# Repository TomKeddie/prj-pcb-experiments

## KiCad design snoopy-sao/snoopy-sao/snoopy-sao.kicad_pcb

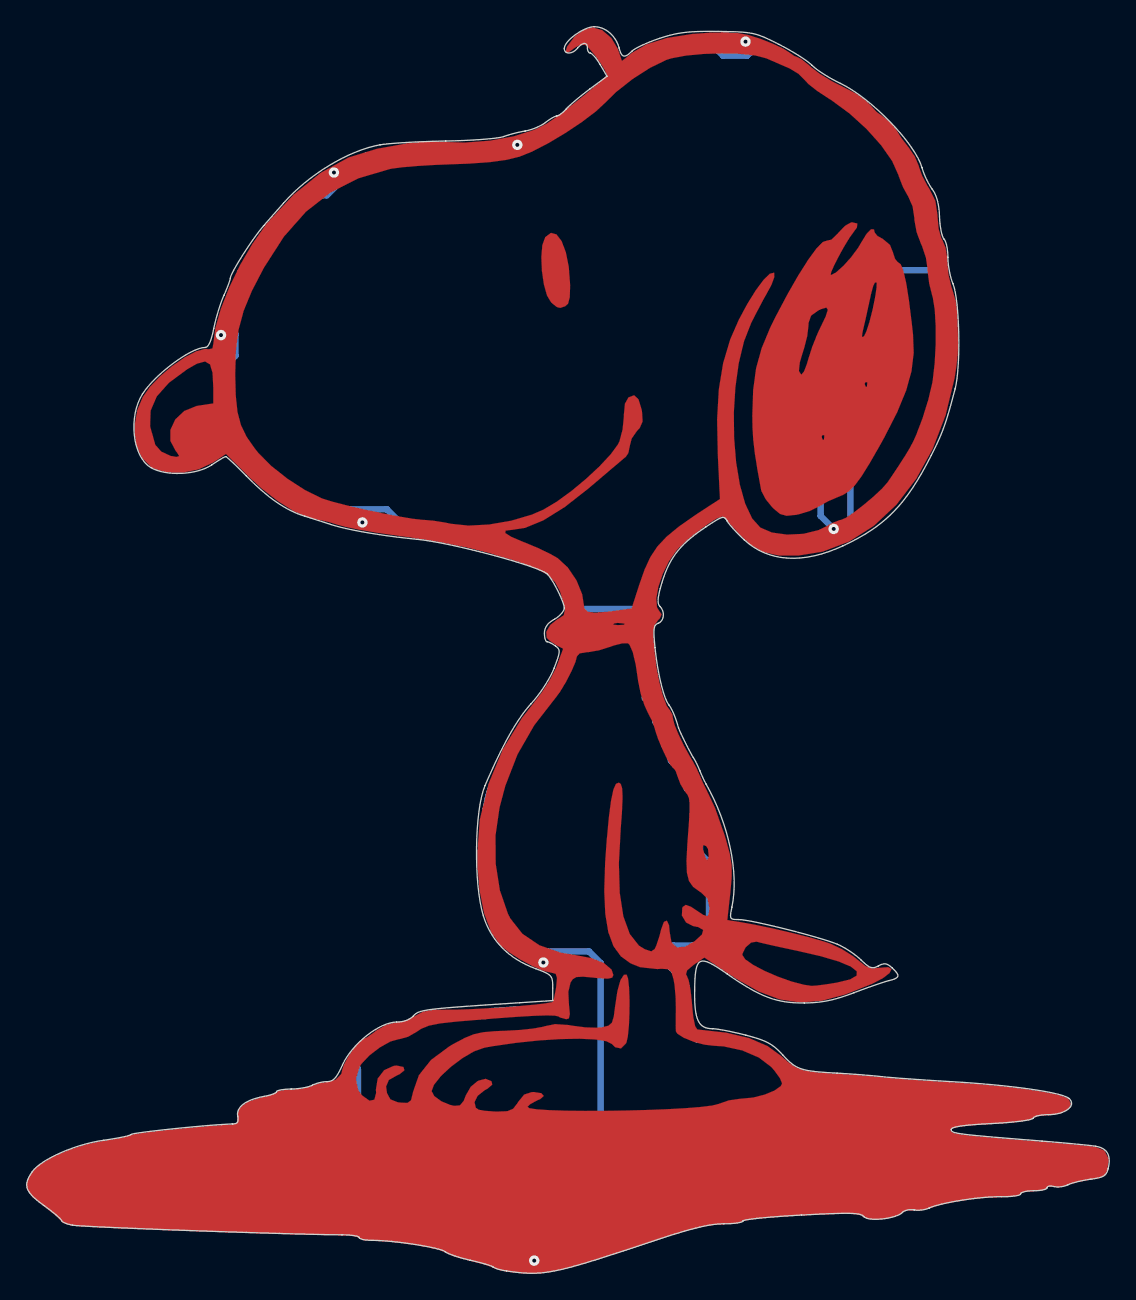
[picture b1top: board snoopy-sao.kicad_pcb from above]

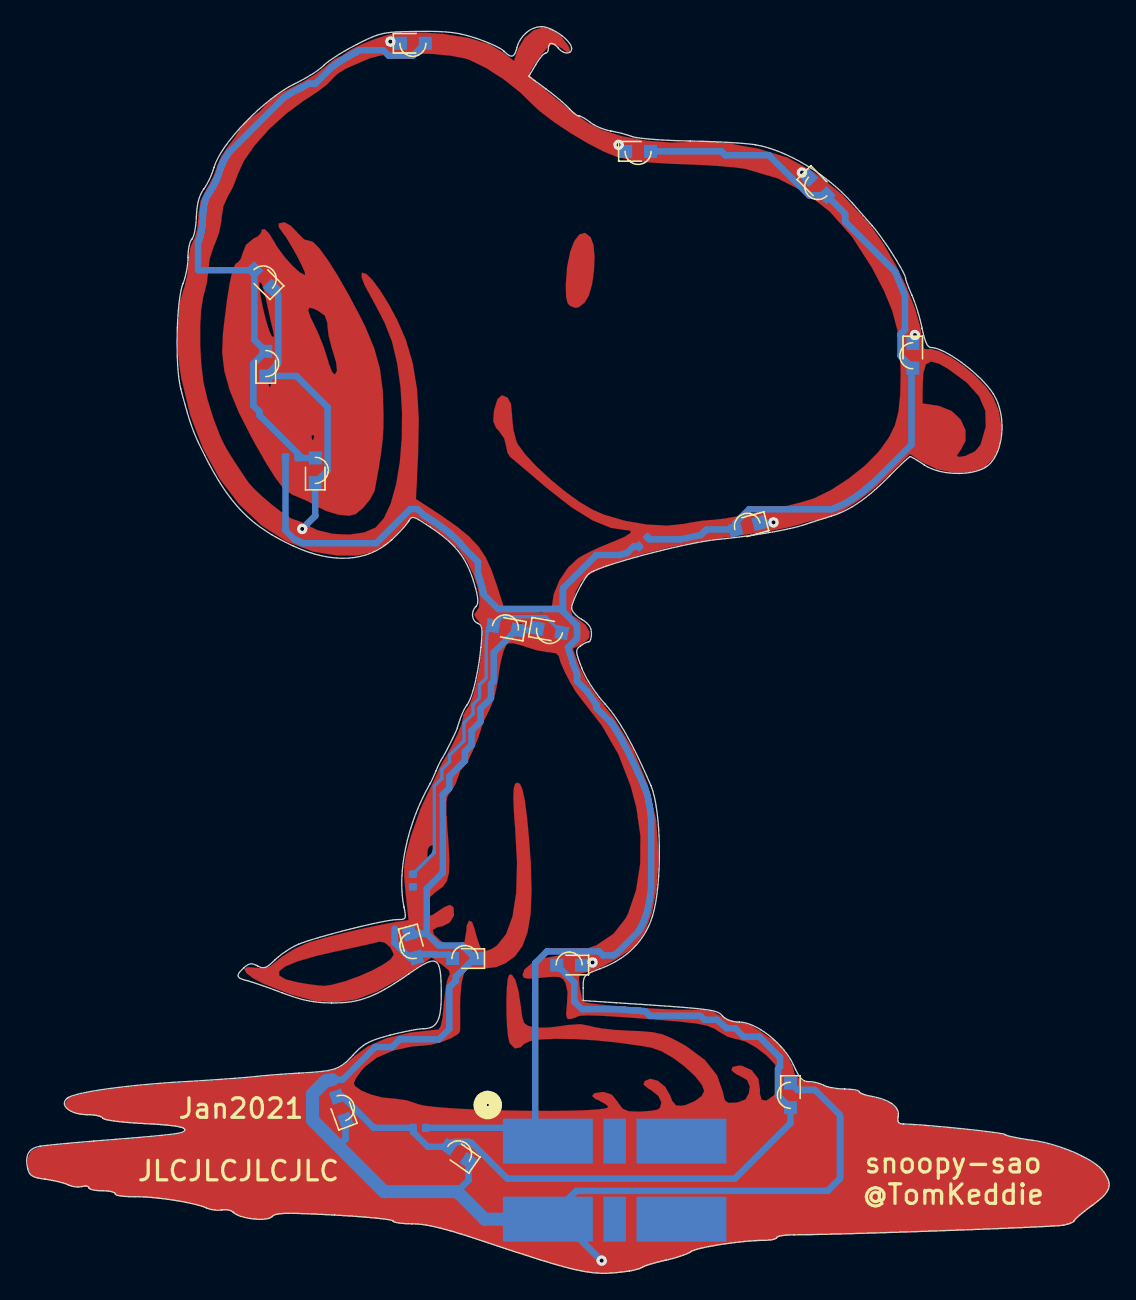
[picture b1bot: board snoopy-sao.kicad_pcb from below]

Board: 2 copper layers, 83.1 x 95.8 mm, 24 parts (21 on the bottom side), 6 nets.

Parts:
D1, D2, D3, D4, D5, D6, D7, D8, D9, D10, D11, D12, D13, D14, D15, D16: LED; ALIEXPRESS_LED_SIDE_0602
H1: front-mask; snoopy-sao-front-mask-invert
H2: front-copper; snoopy-sao-front-copper
H3: back-mask; snoopy-sao-back-mask-invert
R1, R2, R3, R4: 100R; R_0402_1005Metric
X1: Badgelife_sao_connector_v169bis; Badgelife-SAOv169-SAO-2x3-SMD-BIGPADS

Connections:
+3V3: R1.1, R2.1, R3.1, R4.1, X1.1
/A_1: D1.2, D2.2, D3.2, D4.2, R1.2
/A_2: D5.2, D6.2, D7.2, D8.2, R2.2
/A_3: D9.2, D10.2, D11.2, D12.2, R3.2
/A_4: D13.2, D14.2, D15.2, D16.2, R4.2
GND: D1.1, D2.1, D3.1, D4.1, D5.1, D6.1, D7.1, D8.1, D9.1, D10.1, D11.1, D12.1, D13.1, D14.1, D15.1, D16.1, H2.1, X1.2

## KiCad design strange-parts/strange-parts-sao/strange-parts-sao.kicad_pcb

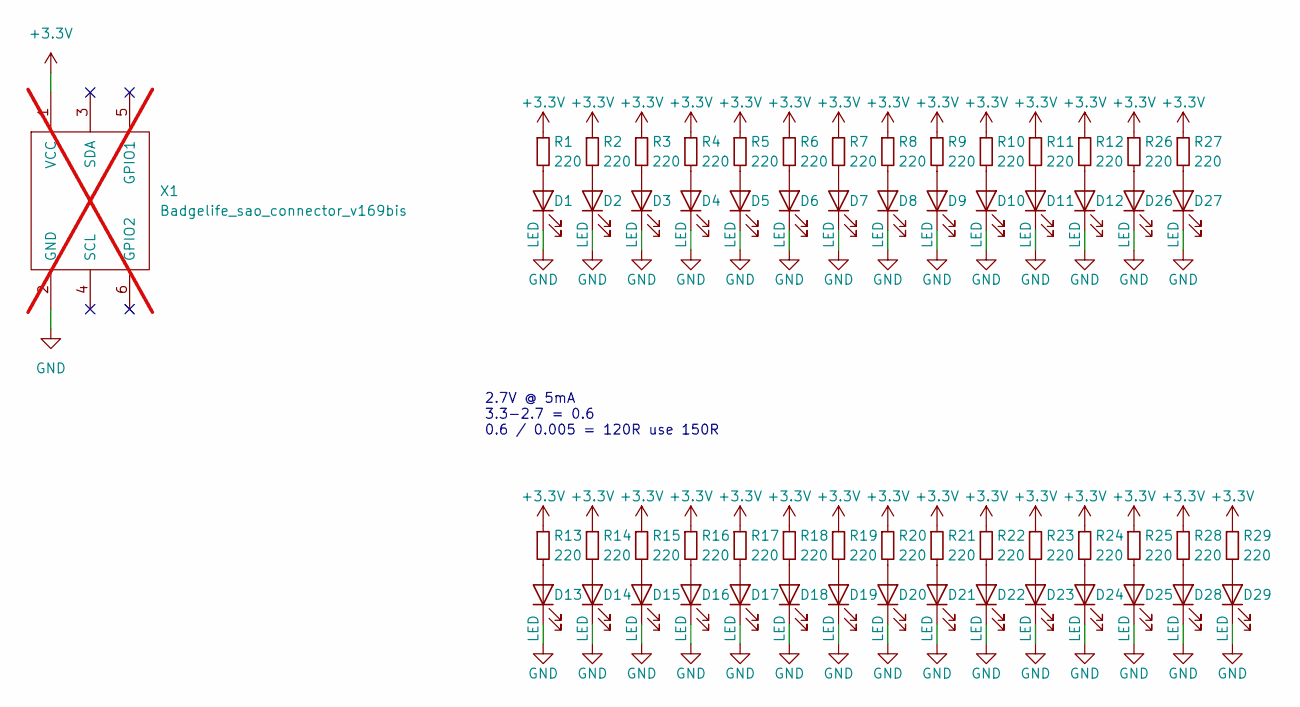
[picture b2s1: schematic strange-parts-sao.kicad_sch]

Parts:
D1, D2, D3, D4, D5, D6, D7, D8, D9, D10, D11, D12, D13, D14, D15, D16, D17, D18, D19, D20, D21, D22, D23, D24, D25, D26, D27, D28, D29: LED; JLCPCB_SIDE_C409529; LCSC C409529
R1, R2, R3, R4, R5, R6, R7, R8, R9, R10, R11, R12, R13, R14, R15, R16, R17, R18, R19, R20, R21, R22, R23, R24, R25, R26, R27, R28, R29: 220; R_0402_1005Metric; MFGPN 0402WGF2200TCE; LCSC C25091
X1: Badgelife_sao_connector_v169bis; Badgelife-SAOv169-SAO-2x3-SMD-BIGPADS; not fitted

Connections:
+3.3V: R1.1, R2.1, R3.1, R4.1, R5.1, R6.1, R7.1, R8.1, R9.1, R10.1, R11.1, R12.1, R13.1, R14.1, R15.1, R16.1, R17.1, R18.1, R19.1, R20.1, R21.1, R22.1, R23.1, R24.1, R25.1, R26.1, R27.1, R28.1, R29.1, X1.1 (VCC)
GND: D1.1 (K), D2.1 (K), D3.1 (K), D4.1 (K), D5.1 (K), D6.1 (K), D7.1 (K), D8.1 (K), D9.1 (K), D10.1 (K), D11.1 (K), D12.1 (K), D13.1 (K), D14.1 (K), D15.1 (K), D16.1 (K), D17.1 (K), D18.1 (K), D19.1 (K), D20.1 (K), D21.1 (K), D22.1 (K), D23.1 (K), D24.1 (K), D25.1 (K), D26.1 (K), D27.1 (K), D28.1 (K), D29.1 (K), X1.2 (GND)
unnamed: D1.2 (A), R1.2
unnamed: D2.2 (A), R2.2
unnamed: D3.2 (A), R3.2
unnamed: D4.2 (A), R4.2
unnamed: D5.2 (A), R5.2
unnamed: D6.2 (A), R6.2
unnamed: D7.2 (A), R7.2
unnamed: D8.2 (A), R8.2
unnamed: D9.2 (A), R9.2
unnamed: D10.2 (A), R10.2
unnamed: D11.2 (A), R11.2
unnamed: D12.2 (A), R12.2
unnamed: D13.2 (A), R13.2
unnamed: D14.2 (A), R14.2
unnamed: D15.2 (A), R15.2
unnamed: D16.2 (A), R16.2
unnamed: D17.2 (A), R17.2
unnamed: D18.2 (A), R18.2
unnamed: D19.2 (A), R19.2
unnamed: D20.2 (A), R20.2
unnamed: D21.2 (A), R21.2
unnamed: D22.2 (A), R22.2
unnamed: D23.2 (A), R23.2
unnamed: D24.2 (A), R24.2
unnamed: D25.2 (A), R25.2
unnamed: D26.2 (A), R26.2
unnamed: D27.2 (A), R27.2
unnamed: D28.2 (A), R28.2
unnamed: D29.2 (A), R29.2

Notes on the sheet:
2.7V @ 5mA 3.3-2.7 = 0.6 0.6 / 0.005 = 120R use 150R

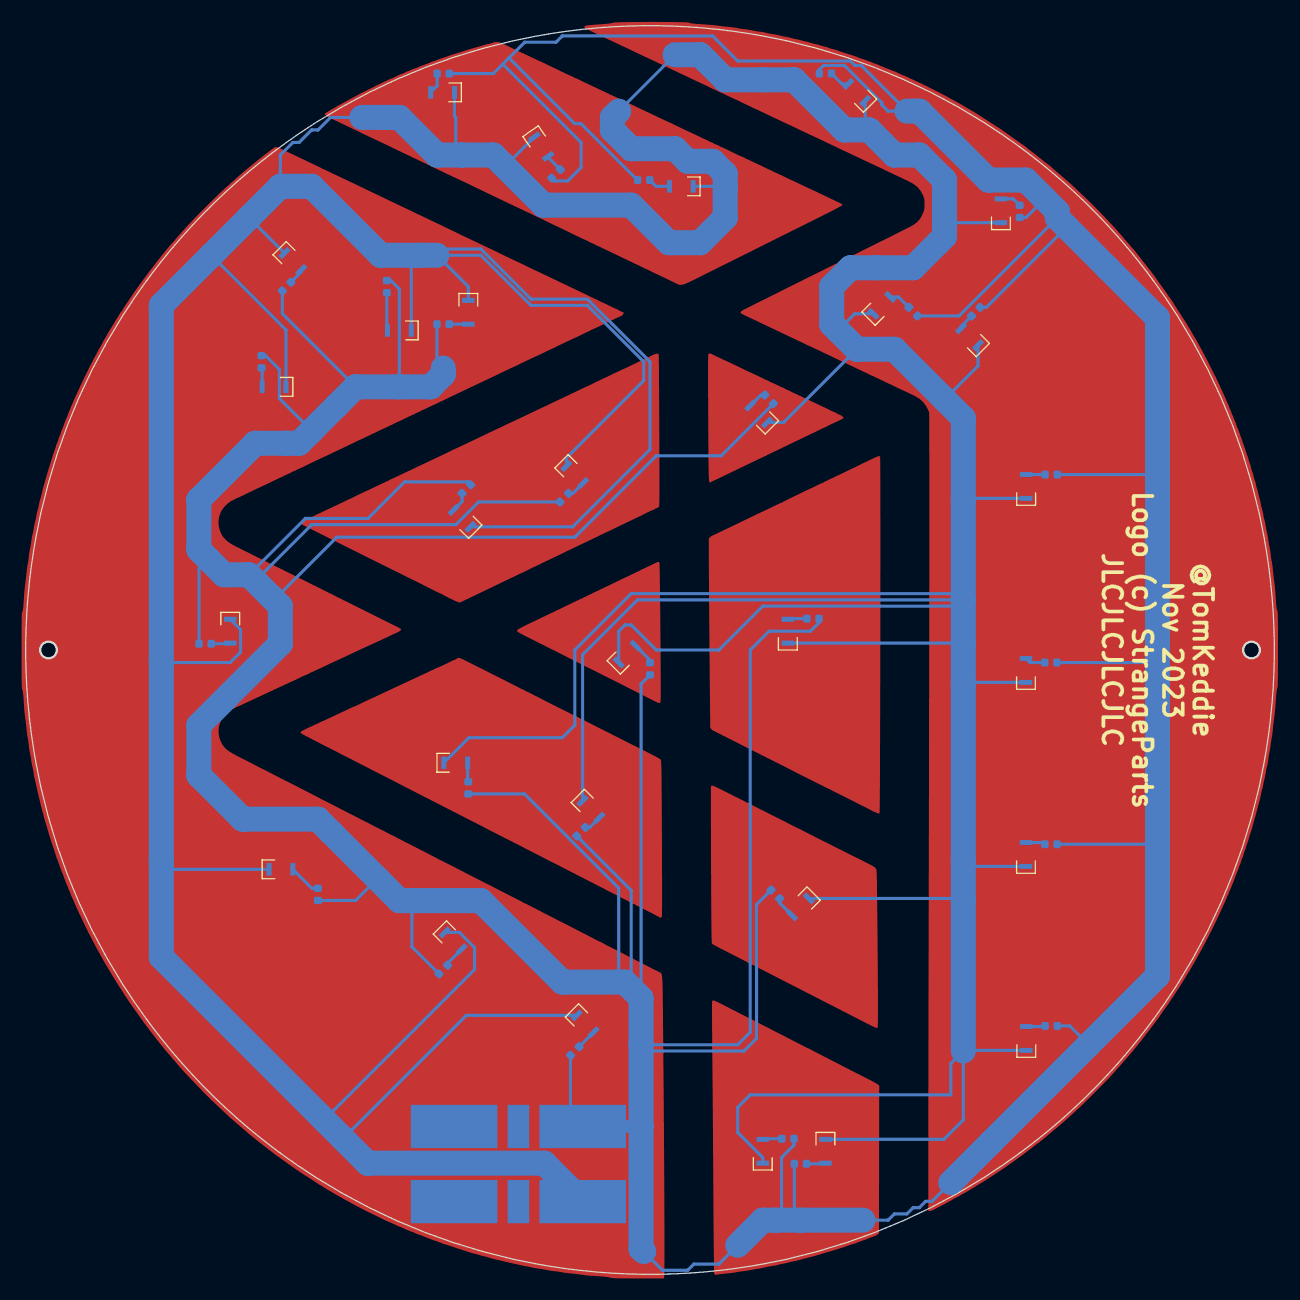
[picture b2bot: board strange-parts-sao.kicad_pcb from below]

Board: 2 copper layers, 99.6 x 99.6 mm, 59 parts (59 on the bottom side), 31 nets.

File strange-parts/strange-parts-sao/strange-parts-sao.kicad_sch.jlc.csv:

"Comment","Designator","Footprint","LCSC"
"LED","D1","tom-opto:JLCPCB_SIDE_C409529","C409529","",""
"LED","D2","tom-opto:JLCPCB_SIDE_C409529","C409529","",""
"LED","D3","tom-opto:JLCPCB_SIDE_C409529","C409529","",""
"LED","D4","tom-opto:JLCPCB_SIDE_C409529","C409529","",""
"LED","D5","tom-opto:JLCPCB_SIDE_C409529","C409529","",""
"LED","D6","tom-opto:JLCPCB_SIDE_C409529","C409529","",""
"LED","D7","tom-opto:JLCPCB_SIDE_C409529","C409529","",""
"LED","D8","tom-opto:JLCPCB_SIDE_C409529","C409529","",""
"LED","D9","tom-opto:JLCPCB_SIDE_C409529","C409529","",""
"LED","D10","tom-opto:JLCPCB_SIDE_C409529","C409529","",""
"LED","D11","tom-opto:JLCPCB_SIDE_C409529","C409529","",""
"LED","D12","tom-opto:JLCPCB_SIDE_C409529","C409529","",""
"LED","D13","tom-opto:JLCPCB_SIDE_C409529","C409529","",""
"LED","D14","tom-opto:JLCPCB_SIDE_C409529","C409529","",""
"LED","D15","tom-opto:JLCPCB_SIDE_C409529","C409529","",""
"LED","D16","tom-opto:JLCPCB_SIDE_C409529","C409529","",""
"LED","D17","tom-opto:JLCPCB_SIDE_C409529","C409529","",""
"LED","D18","tom-opto:JLCPCB_SIDE_C409529","C409529","",""
"LED","D19","tom-opto:JLCPCB_SIDE_C409529","C409529","",""
"LED","D20","tom-opto:JLCPCB_SIDE_C409529","C409529","",""
"LED","D21","tom-opto:JLCPCB_SIDE_C409529","C409529","",""
"LED","D22","tom-opto:JLCPCB_SIDE_C409529","C409529","",""
"LED","D23","tom-opto:JLCPCB_SIDE_C409529","C409529","",""
"LED","D24","tom-opto:JLCPCB_SIDE_C409529","C409529","",""
"LED","D25","tom-opto:JLCPCB_SIDE_C409529","C409529","",""
"LED","D26","tom-opto:JLCPCB_SIDE_C409529","C409529","",""
"LED","D27","tom-opto:JLCPCB_SIDE_C409529","C409529","",""
"LED","D28","tom-opto:JLCPCB_SIDE_C409529","C409529","",""
"LED","D29","tom-opto:JLCPCB_SIDE_C409529","C409529","",""
"220","R1","R_0402_1005Metric","C25091","UNI-ROYAL(Uniroyal Elec)","0402WGF2200TCE"
"220","R2","R_0402_1005Metric","C25091","UNI-ROYAL(Uniroyal Elec)","0402WGF2200TCE"
"220","R3","R_0402_1005Metric","C25091","UNI-ROYAL(Uniroyal Elec)","0402WGF2200TCE"
"220","R4","R_0402_1005Metric","C25091","UNI-ROYAL(Uniroyal Elec)","0402WGF2200TCE"
"220","R5","R_0402_1005Metric","C25091","UNI-ROYAL(Uniroyal Elec)","0402WGF2200TCE"
"220","R6","R_0402_1005Metric","C25091","UNI-ROYAL(Uniroyal Elec)","0402WGF2200TCE"
"220","R7","R_0402_1005Metric","C25091","UNI-ROYAL(Uniroyal Elec)","0402WGF2200TCE"
"220","R8","R_0402_1005Metric","C25091","UNI-ROYAL(Uniroyal Elec)","0402WGF2200TCE"
"220","R9","R_0402_1005Metric","C25091","UNI-ROYAL(Uniroyal Elec)","0402WGF2200TCE"
"220","R10","R_0402_1005Metric","C25091","UNI-ROYAL(Uniroyal Elec)","0402WGF2200TCE"
"220","R11","R_0402_1005Metric","C25091","UNI-ROYAL(Uniroyal Elec)","0402WGF2200TCE"
"220","R12","R_0402_1005Metric","C25091","UNI-ROYAL(Uniroyal Elec)","0402WGF2200TCE"
"220","R13","R_0402_1005Metric","C25091","UNI-ROYAL(Uniroyal Elec)","0402WGF2200TCE"
"220","R14","R_0402_1005Metric","C25091","UNI-ROYAL(Uniroyal Elec)","0402WGF2200TCE"
"220","R15","R_0402_1005Metric","C25091","UNI-ROYAL(Uniroyal Elec)","0402WGF2200TCE"
"220","R16","R_0402_1005Metric","C25091","UNI-ROYAL(Uniroyal Elec)","0402WGF2200TCE"
"220","R17","R_0402_1005Metric","C25091","UNI-ROYAL(Uniroyal Elec)","0402WGF2200TCE"
"220","R18","R_0402_1005Metric","C25091","UNI-ROYAL(Uniroyal Elec)","0402WGF2200TCE"
"220","R19","R_0402_1005Metric","C25091","UNI-ROYAL(Uniroyal Elec)","0402WGF2200TCE"
"220","R20","R_0402_1005Metric","C25091","UNI-ROYAL(Uniroyal Elec)","0402WGF2200TCE"
"220","R21","R_0402_1005Metric","C25091","UNI-ROYAL(Uniroyal Elec)","0402WGF2200TCE"
"220","R22","R_0402_1005Metric","C25091","UNI-ROYAL(Uniroyal Elec)","0402WGF2200TCE"
"220","R23","R_0402_1005Metric","C25091","UNI-ROYAL(Uniroyal Elec)","0402WGF2200TCE"
"220","R24","R_0402_1005Metric","C25091","UNI-ROYAL(Uniroyal Elec)","0402WGF2200TCE"
"220","R25","R_0402_1005Metric","C25091","UNI-ROYAL(Uniroyal Elec)","0402WGF2200TCE"
"220","R26","R_0402_1005Metric","C25091","UNI-ROYAL(Uniroyal Elec)","0402WGF2200TCE"
"220","R27","R_0402_1005Metric","C25091","UNI-ROYAL(Uniroyal Elec)","0402WGF2200TCE"
"220","R28","R_0402_1005Metric","C25091","UNI-ROYAL(Uniroyal Elec)","0402WGF2200TCE"
"220","R29","R_0402_1005Metric","C25091","UNI-ROYAL(Uniroyal Elec)","0402WGF2200TCE"

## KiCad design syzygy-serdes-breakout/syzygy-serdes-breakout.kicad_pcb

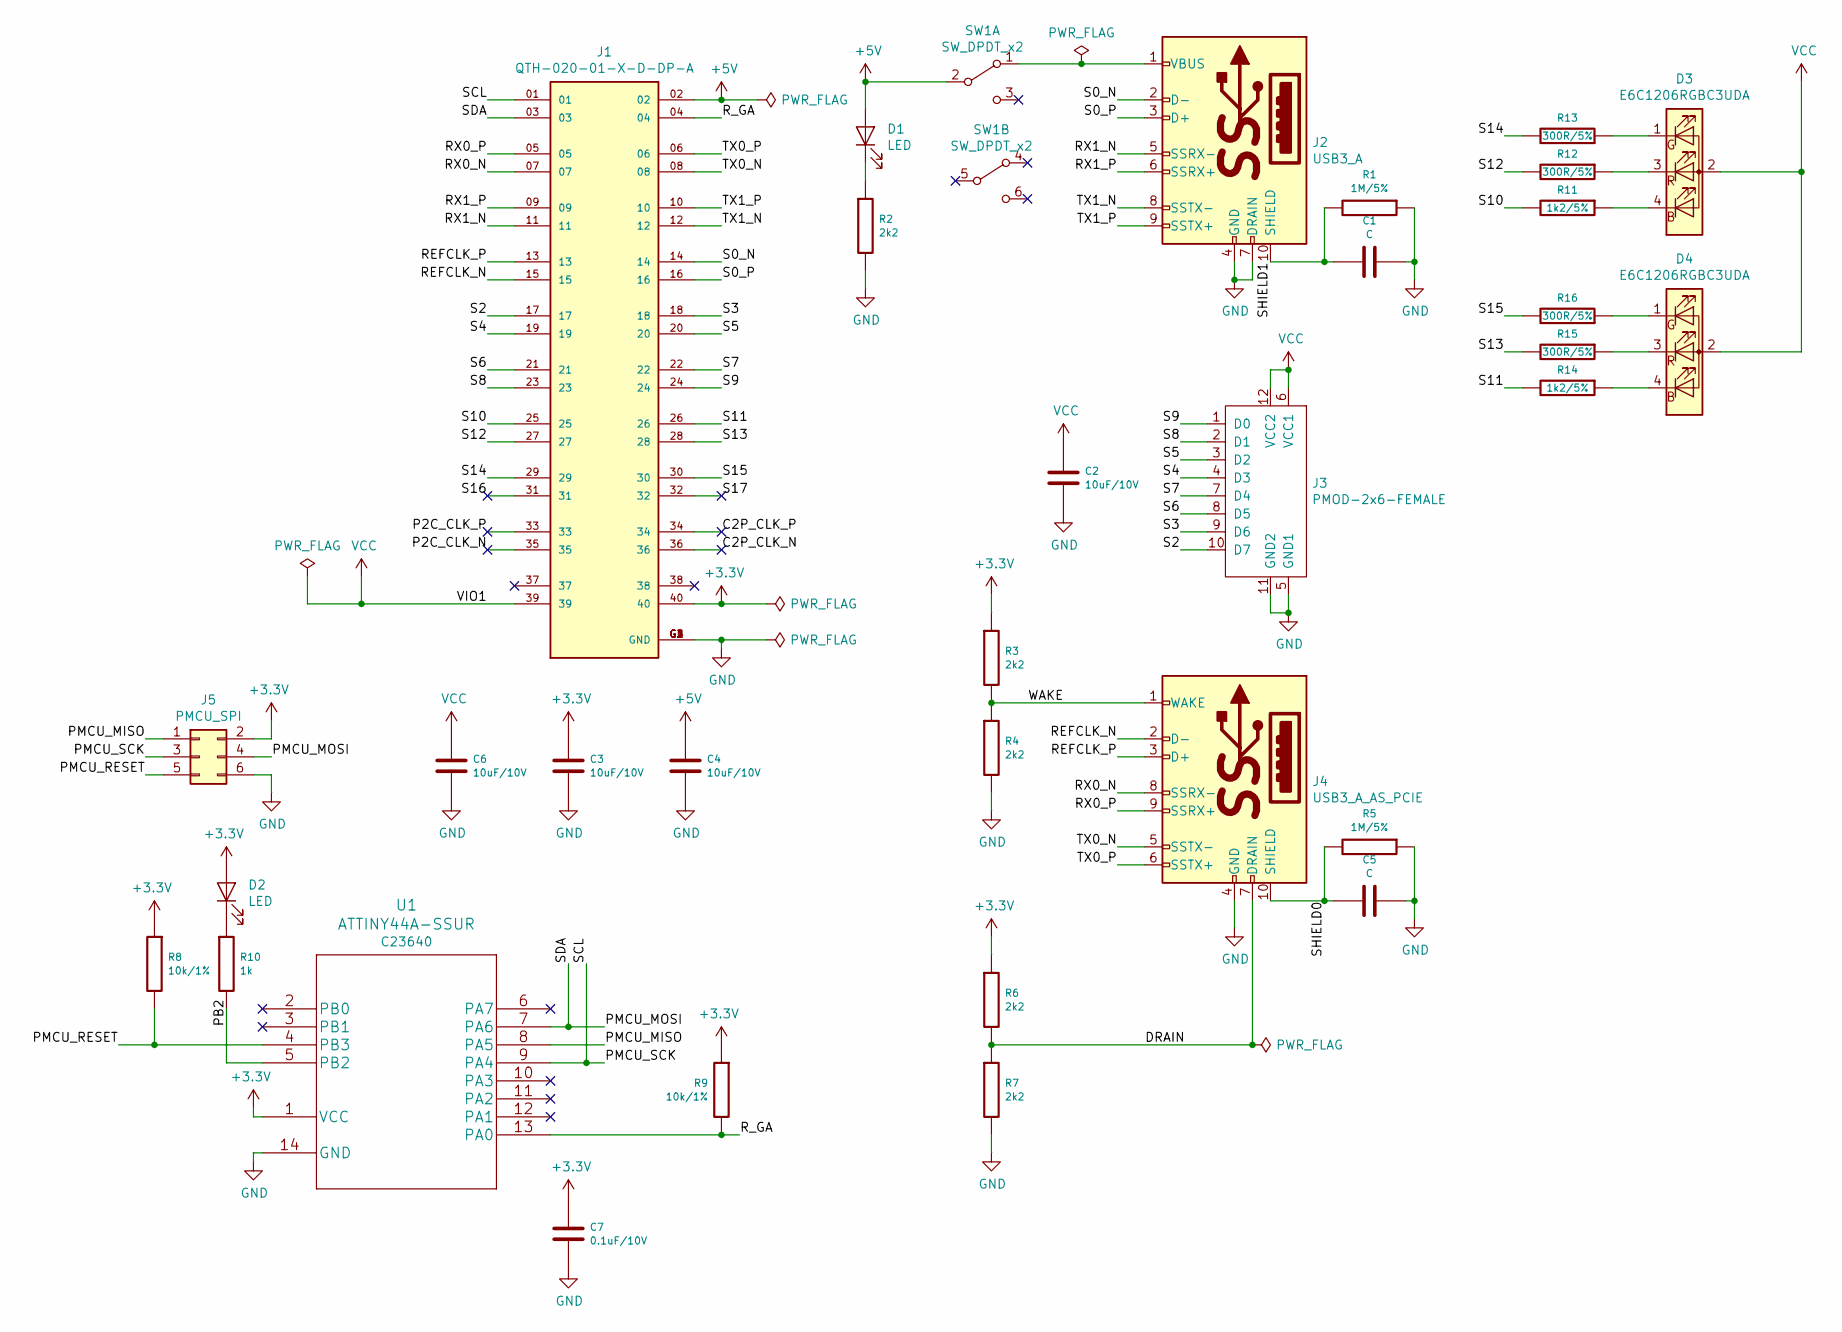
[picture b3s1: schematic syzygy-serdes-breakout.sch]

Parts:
C1, C5: C; C_0603_1608Metric
C2, C3, C4, C6: 10uF/10V; C_0603_1608Metric
C7: 0.1uF/10V; C_0603_1608Metric
D1, D2: LED; LED_0805_2012Metric
D3, D4: E6C1206RGBC3UDA
J1: QTH-020-01-X-D-DP-A; SAMTEC_QTH-020-01-X-D-DP-A; PARTREV L
J2: USB3_A; USB3_A_Aliexpress
J3: PMOD-2x6-FEMALE; PMOD_2X6_PTH_RA_SOCKET
J4: USB3_A_AS_PCIE; USB3_A_Aliexpress
J5: PMCU_SPI; PinHeader_2x03_P2.54mm_Vertical
R1, R5: 1M/5%; R_0603_1608Metric
R2, R3, R4, R6, R7: 2k2; R_0603_1608Metric
R8: 10k/1%; C_0603_1608Metric
R9: 10k/1%; R_0603_1608Metric
R10: 1k; R_0603_1608Metric
R11, R14: 1k2/5%; R_0603_1608Metric
R12, R13, R15, R16: 300R/5%; R_0603_1608Metric
SW1: SW_DPDT_x2; SW_DPDT_SMD
U1: ATTINY44A-SSUR; LCSC C23640

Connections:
+3V3: C3.1, C7.1, D2.2 (A), J1.40, J5.2, R3.1, R6.1, R8.1, R9.1, U1.1 (VCC)
+5V: C4.1, D1.2 (A), J1.02, SW1.2 (B)
/C2P_CLK_N: J1.36
/C2P_CLK_P: J1.34
/DRAIN: J4.7 (DRAIN), R6.2, R7.1
/P2C_CLK_N: J1.35
/P2C_CLK_P: J1.33
/PB2: R10.2, U1.5 (PB2)
/PMCU_MISO: J5.1, U1.8 (PA5)
/PMCU_MOSI: J1.03, J5.4, U1.7 (PA6)
/PMCU_RESET: J5.5, R8.2, U1.4 (PB3)
/PMCU_SCK: J1.01, J5.3, U1.9 (PA4)
/REFCLK_N: J1.15, J4.2 (D-)
/REFCLK_P: J1.13, J4.3 (D+)
/RX0_N: J1.07, J4.8 (SSRX-)
/RX0_P: J1.05, J4.9 (SSRX+)
/RX1_N: J1.11, J2.5 (SSRX-)
/RX1_P: J1.09, J2.6 (SSRX+)
/R_GA: J1.04, R9.2, U1.13 (PA0)
/S0_N: J1.14, J2.2 (D-)
/S0_P: J1.16, J2.3 (D+)
/S2: J1.17, J3.10 (D7)
/S3: J1.18, J3.9 (D6)
/S4: J1.19, J3.4 (D3)
/S5: J1.20, J3.3 (D2)
/S6: J1.21, J3.8 (D5)
/S7: J1.22, J3.7 (D4)
/S8: J1.23, J3.2 (D1)
/S9: J1.24, J3.1 (D0)
/S10: J1.25, R11.2
/S11: J1.26, R14.2
/S12: J1.27, R12.2
/S13: J1.28, R15.2
/S14: J1.29, R13.2
/S15: J1.30, R16.2
/S16: J1.31
/S17: J1.32
/SHIELD0: C5.2, J4.10 (SHIELD), R5.2
/SHIELD1: C1.2, J2.10 (SHIELD), R1.2
/TX0_N: J1.08, J4.5 (SSTX-)
/TX0_P: J1.06, J4.6 (SSTX+)
/TX1_N: J1.12, J2.8 (SSTX-)
/TX1_P: J1.10, J2.9 (SSTX+)
/WAKE: J4.1 (WAKE), R3.2, R4.1
GND: C1.1, C2.2, C3.2, C4.2, C5.1, C6.2, C7.2, J1.G1 (GND), J1.G2 (GND), J1.G3 (GND), J1.G4 (GND), J2.4 (GND), J2.7 (DRAIN), J3.5 (GND1), J3.11 (GND2), J4.4 (GND), J5.6, R1.1, R2.2, R4.2, R5.1, R7.2, U1.14 (GND)
unnamed: D1.1 (K), R2.1
unnamed: D2.1 (K), R10.1
unnamed: D3.1 (G), R13.1
unnamed: D3.3 (R), R12.1
unnamed: D3.4 (B), R11.1
unnamed: D4.1 (G), R16.1
unnamed: D4.3 (R), R15.1
unnamed: D4.4 (B), R14.1
unnamed: J2.1 (VBUS), SW1.1 (A)
VCC: C2.1, C6.1, D3.2 (A), D4.2 (A), J1.39, J3.6 (VCC1), J3.12 (VCC2)

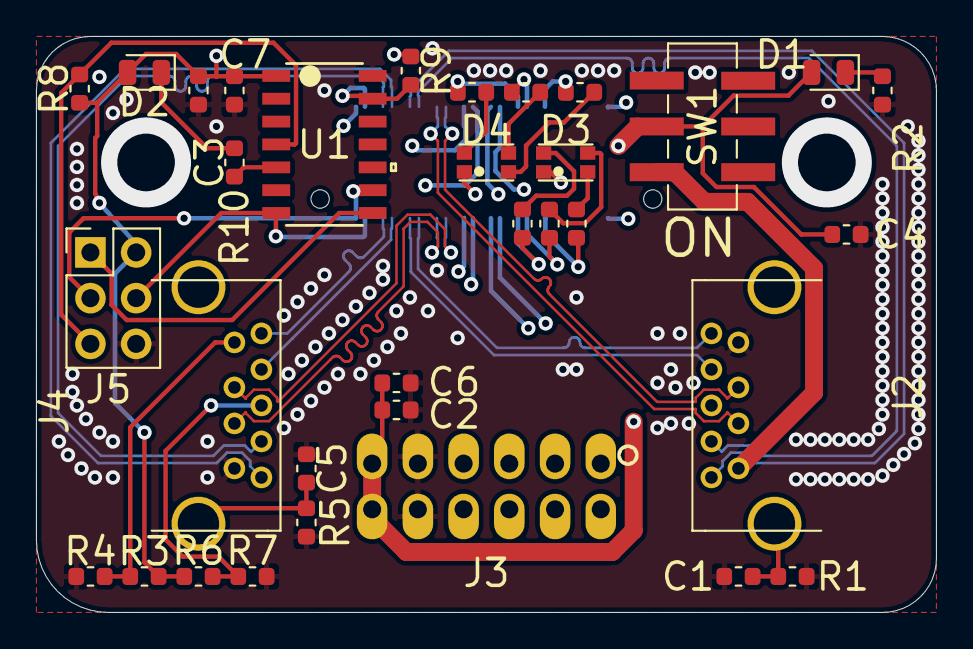
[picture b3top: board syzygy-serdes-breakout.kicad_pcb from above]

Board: 4 copper layers, 50.0 x 32.0 mm, 34 parts (1 on the bottom side), 49 nets.

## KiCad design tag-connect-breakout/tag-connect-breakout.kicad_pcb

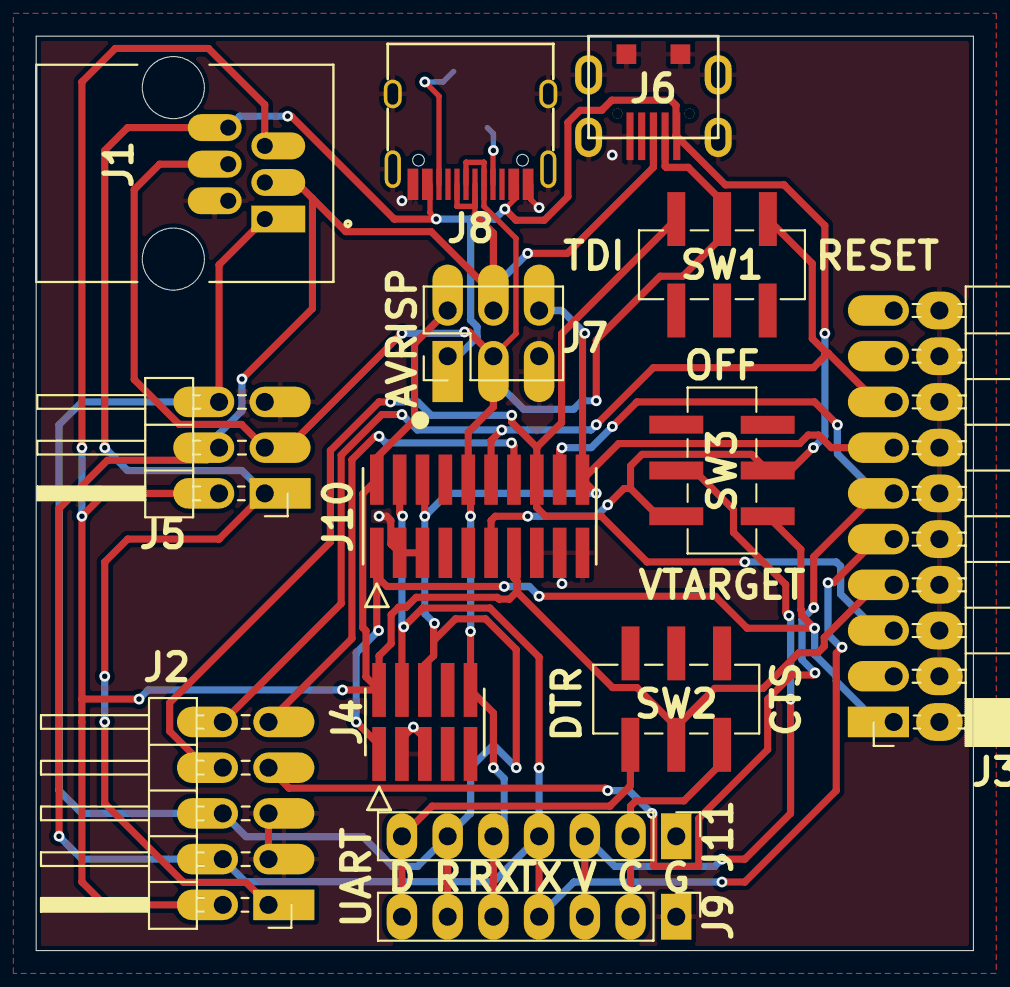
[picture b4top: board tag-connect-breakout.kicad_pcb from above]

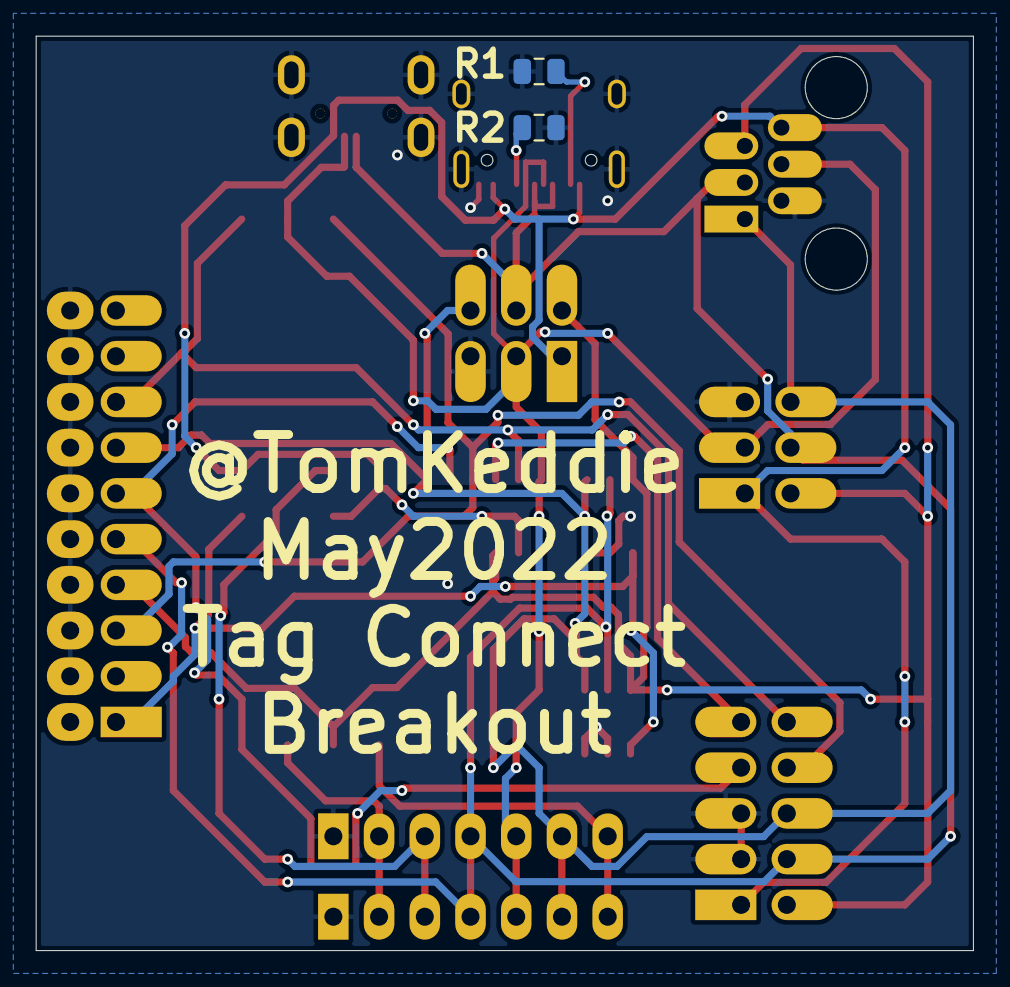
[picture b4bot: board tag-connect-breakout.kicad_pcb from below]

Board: 2 copper layers, 52.1 x 50.8 mm, 16 parts (2 on the bottom side), 16 nets.

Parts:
J1: 6_RJ12; RJ12-6P-6C-SMD-RJE0166001
J2: Conn_02x05_Odd_Even; PinHeader_2x05_P2.54mm_Horizontal
J3: 6_JTAG20; PinSocket_2x10_P2.54mm_Horizontal
J4: CORTEX10; FTSH-105-01-F-DV-K
J5: 6_IDC; PinHeader_2x03_P2.54mm_Horizontal
J6: 6_USB; USB_MICRO_TAOBAO_SMD_PTH
J7: 6_AVR_ISP; PinHeader_2x03_P2.54mm_Vertical
J8: USB_C_Receptacle_USB2.0; USB_C_Receptacle_GT-USB-7010
J9: UART1; PinHeader_1x07_P2.54mm_Vertical
J10: CORTEX20; FTSH-110-01-F-DV-K
J11: UART2; PinHeader_1x07_P2.54mm_Vertical
R1, R2: 5.1k; R_0805_2012Metric
SW1, SW2, SW3: SW_DPDT_x2; SW_DPDT_SMD

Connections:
6-3: J1.4, J4.10, J5.3, J6.2 (D-), J7.3, J8.A7 (D-), J8.B7 (D-), J9.5, J10.10, J11.5, SW1.2 (B)
10-1: J1.6, J2.1, J5.1, J6.1 (VBUS), J7.1, J8.A4 (VBUS), J8.A9 (VBUS), J8.B4 (VBUS), J8.B9 (VBUS), J10.11, SW3.1 (A), SW3.5 (B)
10-2: J1.5, J2.2, J3.7, J4.2, J5.2, J7.2, J10.2, J10.13, SW2.2 (B)
10-3: J1.2, J2.3, J2.5, J3.4, J3.6, J3.8, J3.10, J3.12, J3.14, J3.16, J3.18, J3.20, J4.3, J4.5, J5.5, J6.5 (GND), J6.6 (Shield), J7.5, J8.A1 (GND), J8.A12 (GND), J8.B1 (GND), J8.B12 (GND), J8.S1 (SHIELD), J9.1, J10.3, J10.5, J10.15, J10.17, J10.19, J11.1, R1.1, R2.2
10-4: J1.3, J2.4, J3.9, J4.4, J5.4, J6.3 (D+), J7.4, J8.A6 (D+), J8.B6 (D+), J9.4, J10.4, J11.4
10-6: J1.1, J2.6, J3.13, J4.6, J5.6, J7.6, J9.6, J10.6, J10.20, J11.6
10-7: J2.7, J3.11, J10.18
10-8: J2.8, J3.5, J10.16, SW1.1 (A)
10-9: J2.9, J10.14
10-10: J2.10, J3.15, J10.12, SW1.3 (C)
/UART_VCC_SW: J9.3, J11.3, SW3.2 (B)
/USB_CC1: J8.A5 (CC1), R2.1
/USB_CC2: J8.B5 (CC2), R1.2
JTAG_VCC: J3.1, J4.1, J10.1, SW3.4 (A)
UART_CTS: J9.2, J11.2, SW2.1 (A)
UART_DTR: J9.7, J11.7, SW2.3 (C)

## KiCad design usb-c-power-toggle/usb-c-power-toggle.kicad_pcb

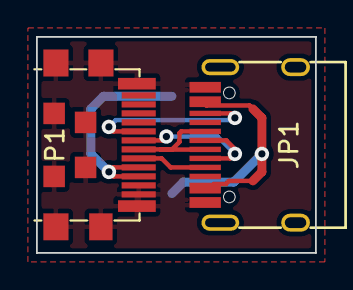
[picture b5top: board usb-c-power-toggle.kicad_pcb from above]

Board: 2 copper layers, 15.5 x 12.0 mm, 3 parts (1 on the bottom side), 7 nets.

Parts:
JP1: USB_C_16PIN; USB_C_Receptacle_GT-USB-7010
P1: USB_C_Plug_USB2.0; USB_C_Plug_UTC009-C12
SW1: Switch_SW_Push_NC; SW_SPST_EVQPE1

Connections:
/CC1: JP1.B5 (CC2), P1.B5 (VCONN)
/CC2: JP1.A5 (CC1), P1.A5 (CC)
/D_N: JP1.A7 (D1-), JP1.B7 (D2-), P1.A7 (D-)
/D_P: JP1.A6 (D1+), JP1.B6 (D2+), P1.A6 (D+)
/VBUS1: P1.A4 (VBUS), P1.B9 (VBUS), SW1.1
/VBUS2: JP1.A4 (VBUS), JP1.A9 (VBUS), JP1.B4 (VBUS), JP1.B9 (VBUS), SW1.2
GND: JP1.A1 (GND), JP1.A12 (GND), JP1.B1 (GND), JP1.B12 (GND), P1.A1 (GND), P1.B12 (GND), P1.S1 (SHIELD)

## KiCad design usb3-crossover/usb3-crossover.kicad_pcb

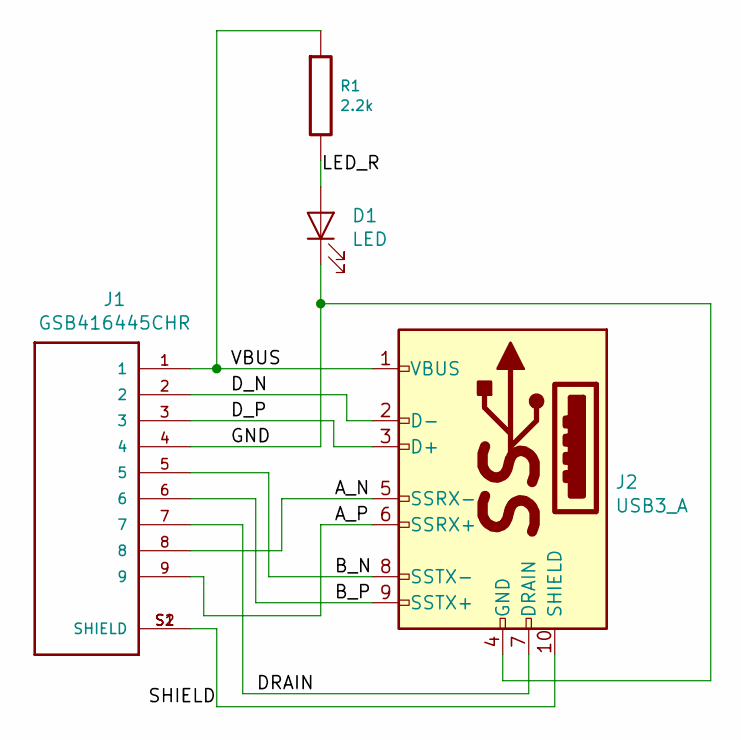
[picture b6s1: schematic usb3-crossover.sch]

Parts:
D1: LED; LED_0805_2012Metric_Pad1.15x1.40mm_HandSolder
J1: GSB416445CHR; AMPHENOL_GSB416445CHR
J2: USB3_A; USB3_A_Aliexpress
R1: 2.2k; R_0603_1608Metric

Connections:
/A_N: J1.8, J2.5 (SSRX-)
/A_P: J1.9, J2.6 (SSRX+)
/B_N: J1.5, J2.8 (SSTX-)
/B_P: J1.6, J2.9 (SSTX+)
/DRAIN: J1.7, J2.7 (DRAIN)
/D_N: J1.2, J2.2 (D-)
/D_P: J1.3, J2.3 (D+)
/GND: D1.1 (K), J1.4, J2.4 (GND)
/LED_R: D1.2 (A), R1.2
/SHIELD: J1.S1 (SHIELD), J1.S2 (SHIELD), J2.10 (SHIELD)
/VBUS: J1.1, J2.1 (VBUS), R1.1

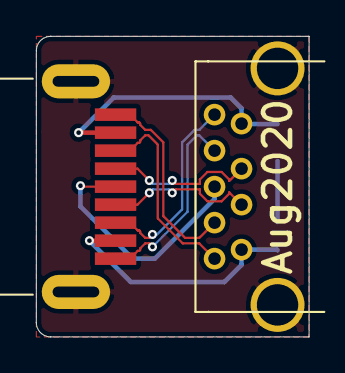
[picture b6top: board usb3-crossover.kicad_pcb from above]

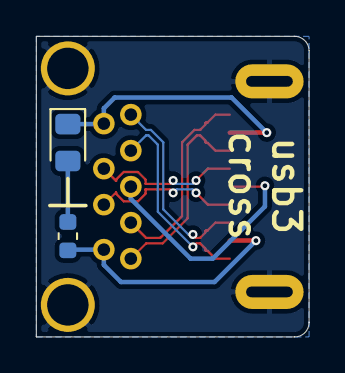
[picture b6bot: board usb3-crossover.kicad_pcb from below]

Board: 2 copper layers, 15.2 x 16.7 mm, 4 parts (2 on the bottom side), 11 nets.

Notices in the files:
parts and their libraries:
Copyright 2016 Accelerated Designs. All rights reserved.
